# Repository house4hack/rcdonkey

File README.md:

RC Donkey
====

Based on the excellent project by Will Roscoe [https://github.com/wroscoe/donkey]

Simplified to use RC during training and driving - removing the need for WiFi and control using smartphone.

Talk from SatRDay included as a branch.

To automate running donkeyreader:

```
---------------------------------------------------

pi@raspberrypi:~ $ cat /etc/init.d/run_ai.sh
#!/bin/bash
### BEGIN INIT INFO
# Provides:          sample.py
# Required-Start:    $remote_fs $syslog
# Required-Stop:     $remote_fs $syslog
# Default-Start:     2 3 4 5
# Default-Stop:      0 1 6
# Short-Description: Start daemon at boot time
# Description:       Enable service provided by daemon.
### END INIT INFO

cd /home/pi/rcdonkey/donkeyreader/
./run.sh
pi@raspberrypi:~ $

pi@raspberrypi:~ $ sudo chmod +x /etc/init.d/run_ai.sh
pi@raspberrypi:~ $ sudo update-rc.d run_ai.sh defaults
pi@raspberrypi:~ $ sudo reboot

Done, once your Raspi booted up run.sh (donkeyreader) should already run in the background
---------------------------------------------------
```

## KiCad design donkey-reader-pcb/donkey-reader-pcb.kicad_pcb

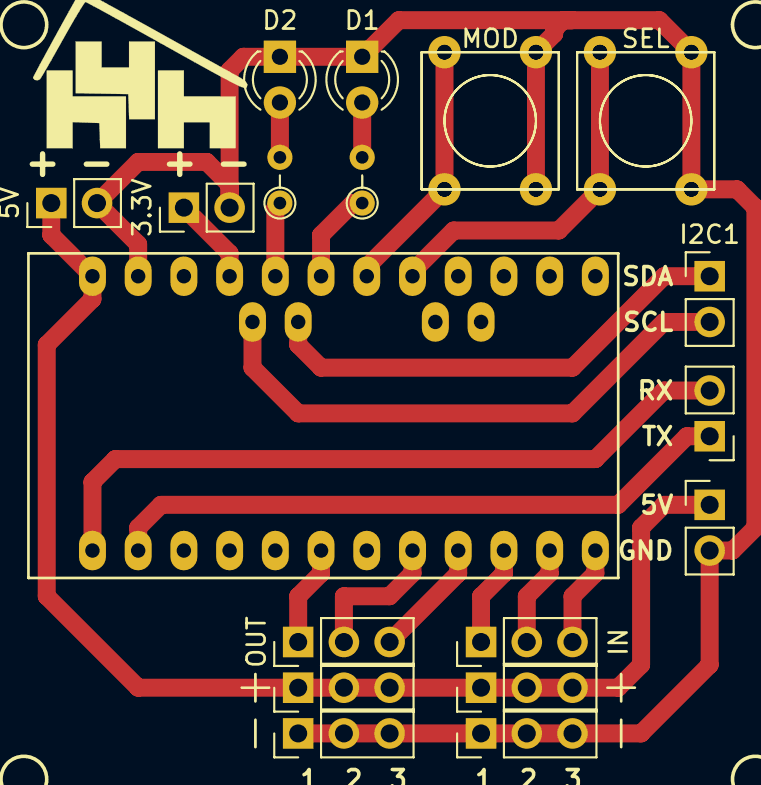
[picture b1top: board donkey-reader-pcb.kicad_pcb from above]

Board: 2 copper layers, 20 parts (0 on the bottom side), 19 nets.

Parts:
3.3V, 5V: CONN_01X02; Pin_Header_Straight_1x02_Pitch2.54mm
+: CONN_01X03; Pin_Header_Straight_1x03_Pitch2.54mm
+#2: CONN_01X03; Pin_Header_Straight_1x03_Pitch2.54mm
-: CONN_01X03; Pin_Header_Straight_1x03_Pitch2.54mm
-#2: CONN_01X03; Pin_Header_Straight_1x03_Pitch2.54mm
D1, D2: LED; LED_D3.0mm
I2C1: CONN_01X02; Pin_Header_Straight_1x02_Pitch2.54mm
IC1: ArduinoProMini; pro_mini
IN: CONN_01X03; Pin_Header_Straight_1x03_Pitch2.54mm
MOD: SW_PUSH; SW_PUSH_SMALL
OUT: CONN_01X03; Pin_Header_Straight_1x03_Pitch2.54mm
PI: PI; Pin_Header_Straight_1x02_Pitch2.54mm
R1, R2: R; R_Axial_DIN0204_L3.6mm_D1.6mm_P2.54mm_Vertical
RX: CONN_01X02; Pin_Header_Straight_1x02_Pitch2.54mm
SEL: SW_PUSH; SW_PUSH_SMALL
SW1, SW2: SW_PUSH; SW_PUSH_SMALL

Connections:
+3V3: 3.3V.1, IC1.21
+5V: 5V.1, +.1, +.2, +.3, +#2.1, +#2.2, +#2.3, IC1.24, PI.1
GND: 3.3V.2, 5V.2, -.1, -.2, -.3, -#2.1, -#2.2, -#2.3, D1.1, D2.1, IC1.4, IC1.23, MOD.2, PI.2, SEL.2, SW1.2, SW2.2
LED1: IC1.19, R1.1
LED2: IC1.20, R2.1
unnamed: D1.2, R1.2
unnamed: D2.2, R2.2
unnamed: IC1.1, RX.2
unnamed: IC1.2, RX.1
unnamed: IC1.6, OUT.1
unnamed: IC1.8, OUT.2
unnamed: IC1.9, OUT.3
unnamed: IC1.10, IN.1
unnamed: IC1.11, IN.2
unnamed: IC1.12, IN.3
SCL: I2C1.2, IC1.26
SDA: I2C1.1, IC1.25
SW1: IC1.17, SEL.1, SW1.1
SW2: IC1.18, MOD.1, SW2.1

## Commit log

2017-06-10 binary protocol
2017-06-10 Mode buttons
2017-06-10 mode buttons on python
2017-06-10 servo util and configfile
2017-06-10 debug comms
2017-06-10 calibration
2017-06-13 arduino recordmode
2017-06-13 record into folders
2017-06-13 recording into seperate folders
2017-06-13 Added mount and umount functions to util.py Added mount and umount calls in donkeyreader.py This would make record button mount the USB flash drive Pressing the record button to stop the recording sh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
2017-06-13 Disable mode on arduino
2017-06-13 All your base are belong to us
2017-06-13 is_deciding mounting
2017-06-13 Changed config
2017-06-13 ihdf5
2017-06-13 Moved h5 stuff
2017-06-13 Speed up pilot loading
2017-06-13 bug fixes
2017-06-15 more robust mounting and unmounting
2017-06-15 removed opencv depency and using donkey camera
2017-06-15 angle from -1 to 1
2017-06-16 Car idling added
2017-06-17 moved model into /home/pi/record/model folder
2017-06-17 Prevent car run-away in auto mode
2017-06-17 Fixed predicting of throttle
2017-07-04 Running median
2018-02-28 Remove donkey imports
2018-03-11 fixes
2018-03-17 satrday
2018-03-17 README
2018-03-17 Clean up notebook
